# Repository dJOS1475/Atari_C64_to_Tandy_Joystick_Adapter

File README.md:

# Atari_C64_to_Tandy_Joystick_Adapter
Atari and C64 to Tandy Joystick Adapter

Use your Digital Commodore 64 or Atari compatible joysticks on your Tandy 1000 or CoCo Computer! Perfect for playing arcade-style games that require precision movements that can only be delivered via a classic micro-switch equipped digital joystick. eg a Competition Pro.

This Adapter supports 2 fire buttons for joysticks with 2 discrete Fire buttons.

My Store can be found here: https://www.tindie.com/stores/CyberneticSys/

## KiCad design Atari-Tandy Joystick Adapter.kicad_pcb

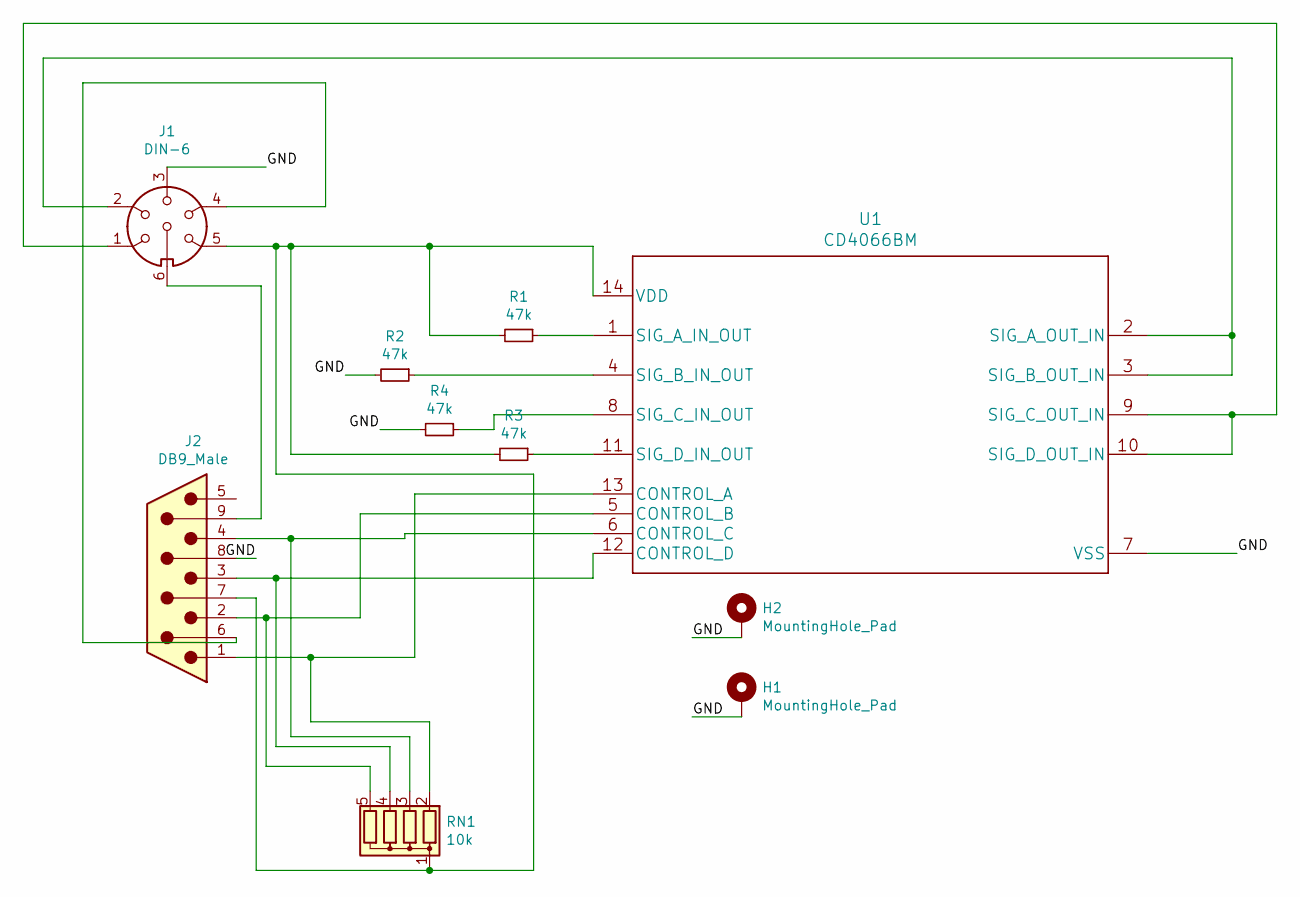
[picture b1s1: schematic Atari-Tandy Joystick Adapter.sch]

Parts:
H1, H2: MountingHole_Pad; MountingHole_4.3mm_M4_DIN965_Pad
J1: DIN-6; PinSocket_1x06_P2.54mm_Vertical
J2: DB9_Male; DSUB-9_Male_Horizontal_P2.77x2.84mm_EdgePinOffset4.94mm_Hou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
R1, R2, R3, R4: 47k; R_Axial_DIN0309_L9.0mm_D3.2mm_P15.24mm_Horizontal
RN1: 10k; R_Array_SIP5
U1: CD4066BM

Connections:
/GND: H1.1, H2.1, J1.3, J2.8, R2.2, R4.2, U1.7 (VSS)
unnamed: J1.1, U1.9 (SIG_C_OUT_IN), U1.10 (SIG_D_OUT_IN)
unnamed: J1.2, U1.2 (SIG_A_OUT_IN), U1.3 (SIG_B_OUT_IN)
unnamed: J1.4, J2.6
unnamed: J1.5, J2.7, R1.2, R3.2, RN1.1 (common), U1.14 (VDD)
unnamed: J1.6, J2.9
unnamed: J2.1, RN1.2 (R1), U1.13 (CONTROL_A)
unnamed: J2.2, RN1.5 (R4), U1.5 (CONTROL_B)
unnamed: J2.3, RN1.4 (R3), U1.12 (CONTROL_D)
unnamed: J2.4, RN1.3 (R2), U1.6 (CONTROL_C)
unnamed: R1.1, U1.1 (SIG_A_IN_OUT)
unnamed: R2.1, U1.4 (SIG_B_IN_OUT)
unnamed: R3.1, U1.11 (SIG_D_IN_OUT)
unnamed: R4.1, U1.8 (SIG_C_IN_OUT)

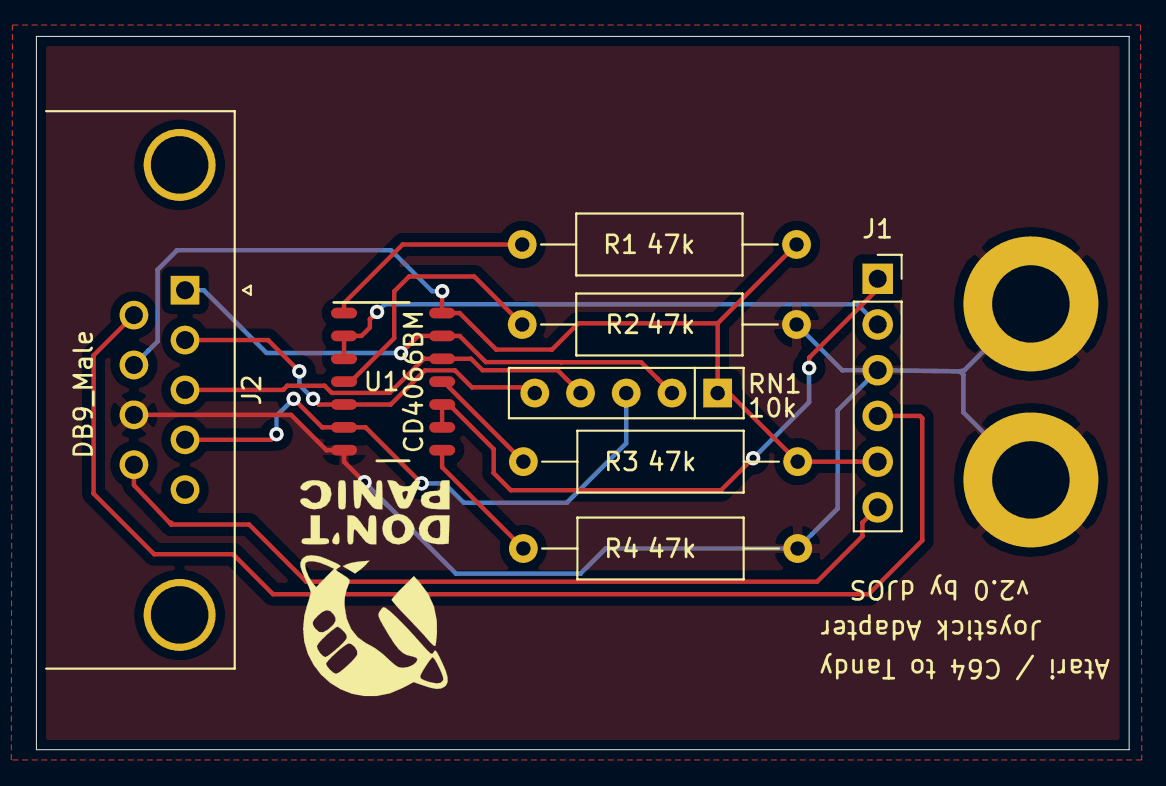
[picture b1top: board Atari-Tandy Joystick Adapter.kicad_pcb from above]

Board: 2 copper layers, 60.7 x 39.6 mm, 10 parts (0 on the bottom side), 14 nets.

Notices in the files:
parts and their libraries:
Copyright 2016 Accelerated Designs. All rights reserved.
